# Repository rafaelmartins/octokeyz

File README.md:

# octokeyz

A USB macropad you program with Go.

For documentation please visit: https://octokeyz.rgm.io/

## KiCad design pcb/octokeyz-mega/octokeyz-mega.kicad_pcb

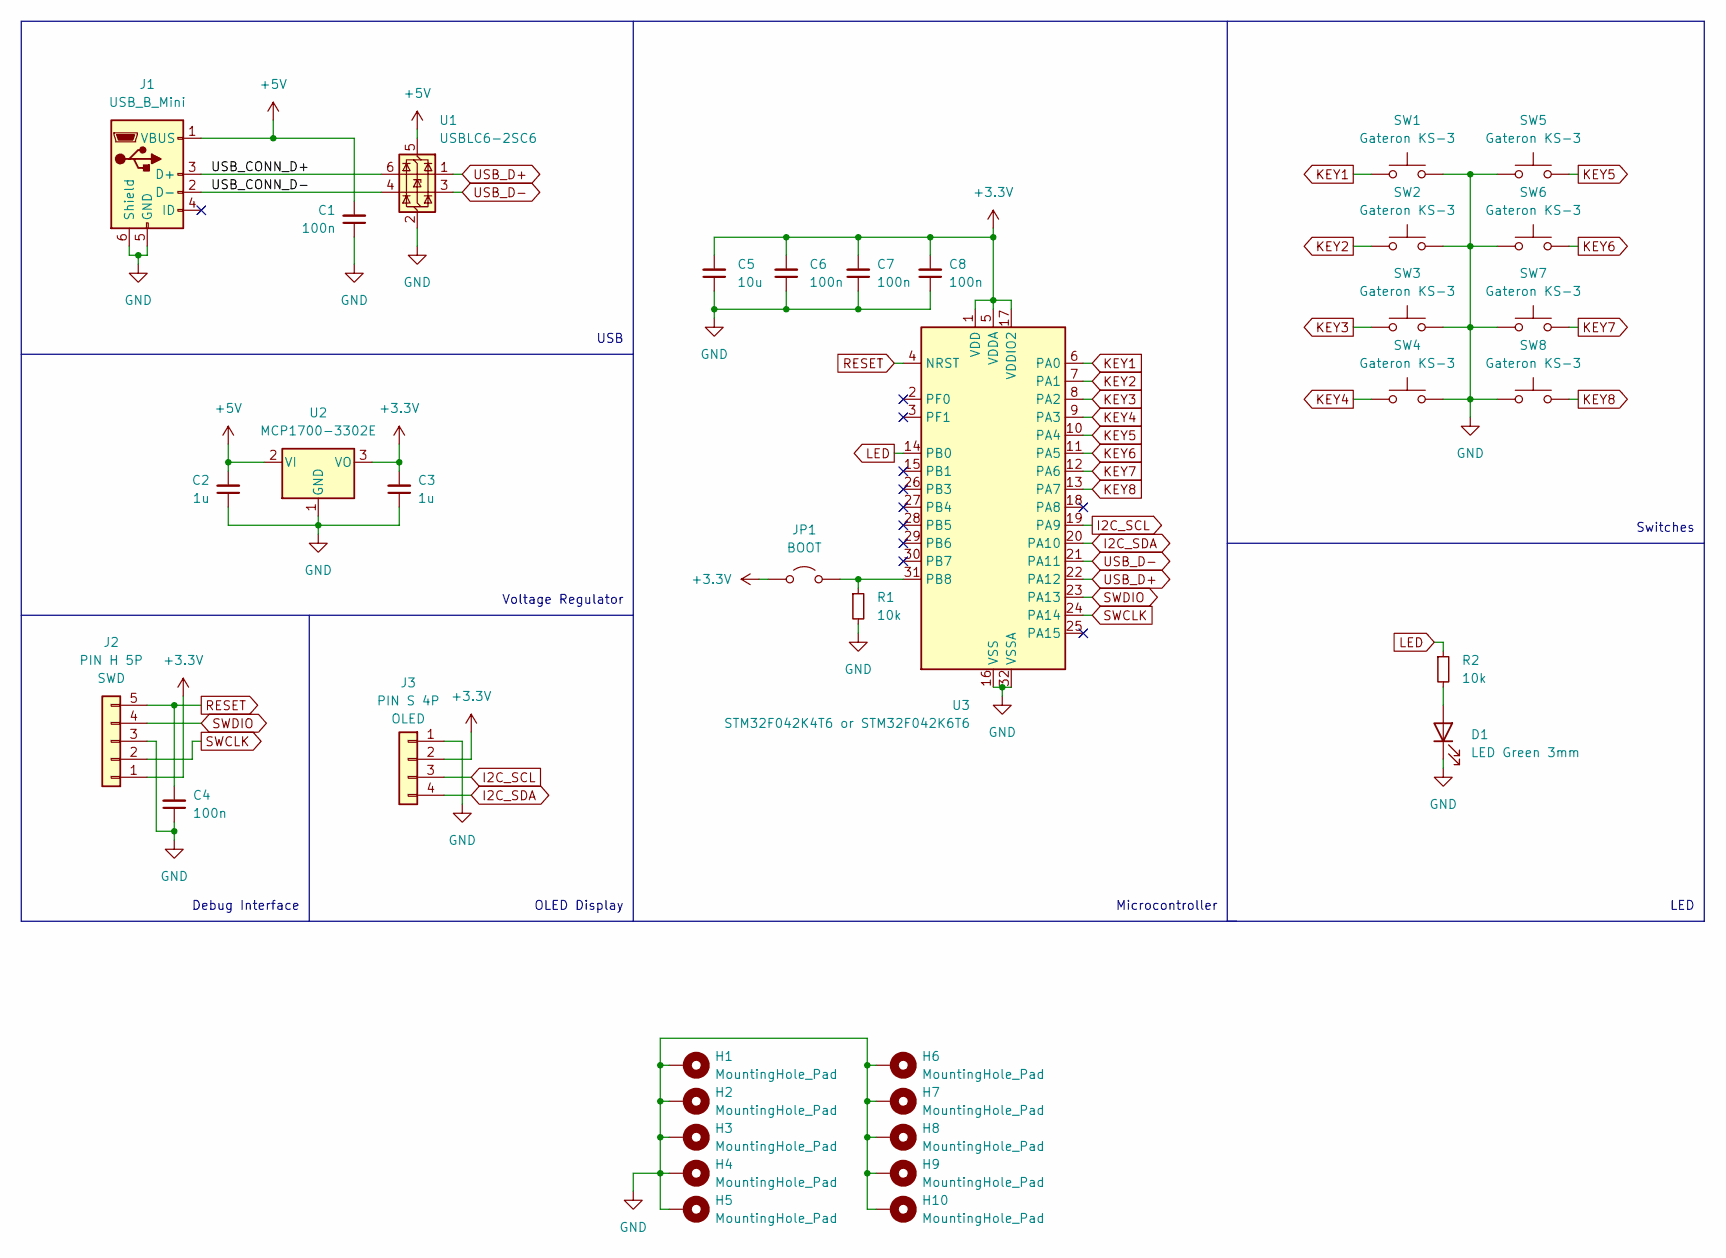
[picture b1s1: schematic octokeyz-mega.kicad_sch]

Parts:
C1, C4, C6, C7, C8: 100n; C_TDK_FA28; MPN FA28X7R1H104KNU06
C2, C3: 1u; C_TDK_FA28; MPN FA28X7R1E105KRU06
C5: 10u; C_TDK_FA26; MPN FA26X7R1E106KRU06
D1: LED Green 3mm; LED_D3.0mm; MPN OVLBG4C7
H1, H2, H3, H4, H5, H6, H7, H8, H9, H10: MountingHole_Pad; MountingHole_2.2mm_M2_Pad_Via
J1: USB_B_Mini; USB_Mini-B_PTH; MPN GMSB0522132EU
J2: PIN H 5P; PinHeader_1x05_P2.54mm_Horizontal
J3: PIN S 4P; PinSocket_1x04_P2.54mm_Vertical; MPN PPPC041LFBN-RC
JP1: BOOT; PinHeader_1x02_P2.54mm_Horizontal
R1, R2: 10k; R_YAGEO_MFR-25FTE52_Horizontal; MPN MFR-25FTE52-10K
SW1, SW2, SW3, SW4, SW5, SW6, SW7, SW8: Gateron KS-3; SW_Cherry_MX_1.00u_PCB; MPN Gateron KS-3
U1: USBLC6-2SC6; SOT-23-6; MPN USBLC6-2SC6
U2: MCP1700-3302E; TO-92_Inline_Wide; MPN MCP1700-3302E/TO
U3: STM32F042K4T6 or STM32F042K6T6; LQFP-32_7x7mm_P0.8mm; MPN STM32F042K6T6

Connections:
+3.3V: C3.2, C5.2, C6.2, C7.2, C8.2, J2.1, J3.2, JP1.2 (B), U2.3 (VO), U3.1 (VDD), U3.5 (VDDA), U3.17 (VDDIO2)
+5V: C1.2, C2.2, J1.1 (VBUS), U1.5 (VBUS), U2.2 (VI)
/USB_CONN_D+: J1.3 (D+), U1.6 (I/O1)
/USB_CONN_D-: J1.2 (D-), U1.4 (I/O2)
GND: C1.1, C2.1, C3.1, C4.1, C5.1, C6.1, C7.1, C8.1, D1.1 (K), H1.1, H2.1, H3.1, H4.1, H5.1, H6.1, H7.1, H8.1, H9.1, H10.1, J1.5 (GND), J1.6 (Shield), J2.3, J3.1, R1.2, SW1.2, SW2.2, SW3.2, SW4.2, SW5.2, SW6.2, SW7.2, SW8.2, U1.2 (GND), U2.1 (GND), U3.16 (VSS), U3.32 (VSSA)
I2C_SCL: J3.3, U3.19 (PA9)
I2C_SDA: J3.4, U3.20 (PA10)
KEY1: SW1.1, U3.6 (PA0)
KEY2: SW2.1, U3.7 (PA1)
KEY3: SW3.1, U3.8 (PA2)
KEY4: SW4.1, U3.9 (PA3)
KEY5: SW5.1, U3.10 (PA4)
KEY6: SW6.1, U3.11 (PA5)
KEY7: SW7.1, U3.12 (PA6)
KEY8: SW8.1, U3.13 (PA7)
LED: R2.1, U3.14 (PB0)
unnamed: D1.2 (A), R2.2
unnamed: JP1.1 (A), R1.1, U3.31 (PB8)
RESET: C4.2, J2.5, U3.4 (NRST)
SWCLK: J2.2, U3.24 (PA14)
SWDIO: J2.4, U3.23 (PA13)
USB_D+: U1.1 (I/O1), U3.22 (PA12)
USB_D-: U1.3 (I/O2), U3.21 (PA11)

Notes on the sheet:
Switches
OLED Display
Microcontroller
LED
Debug Interface
USB
Voltage Regulator

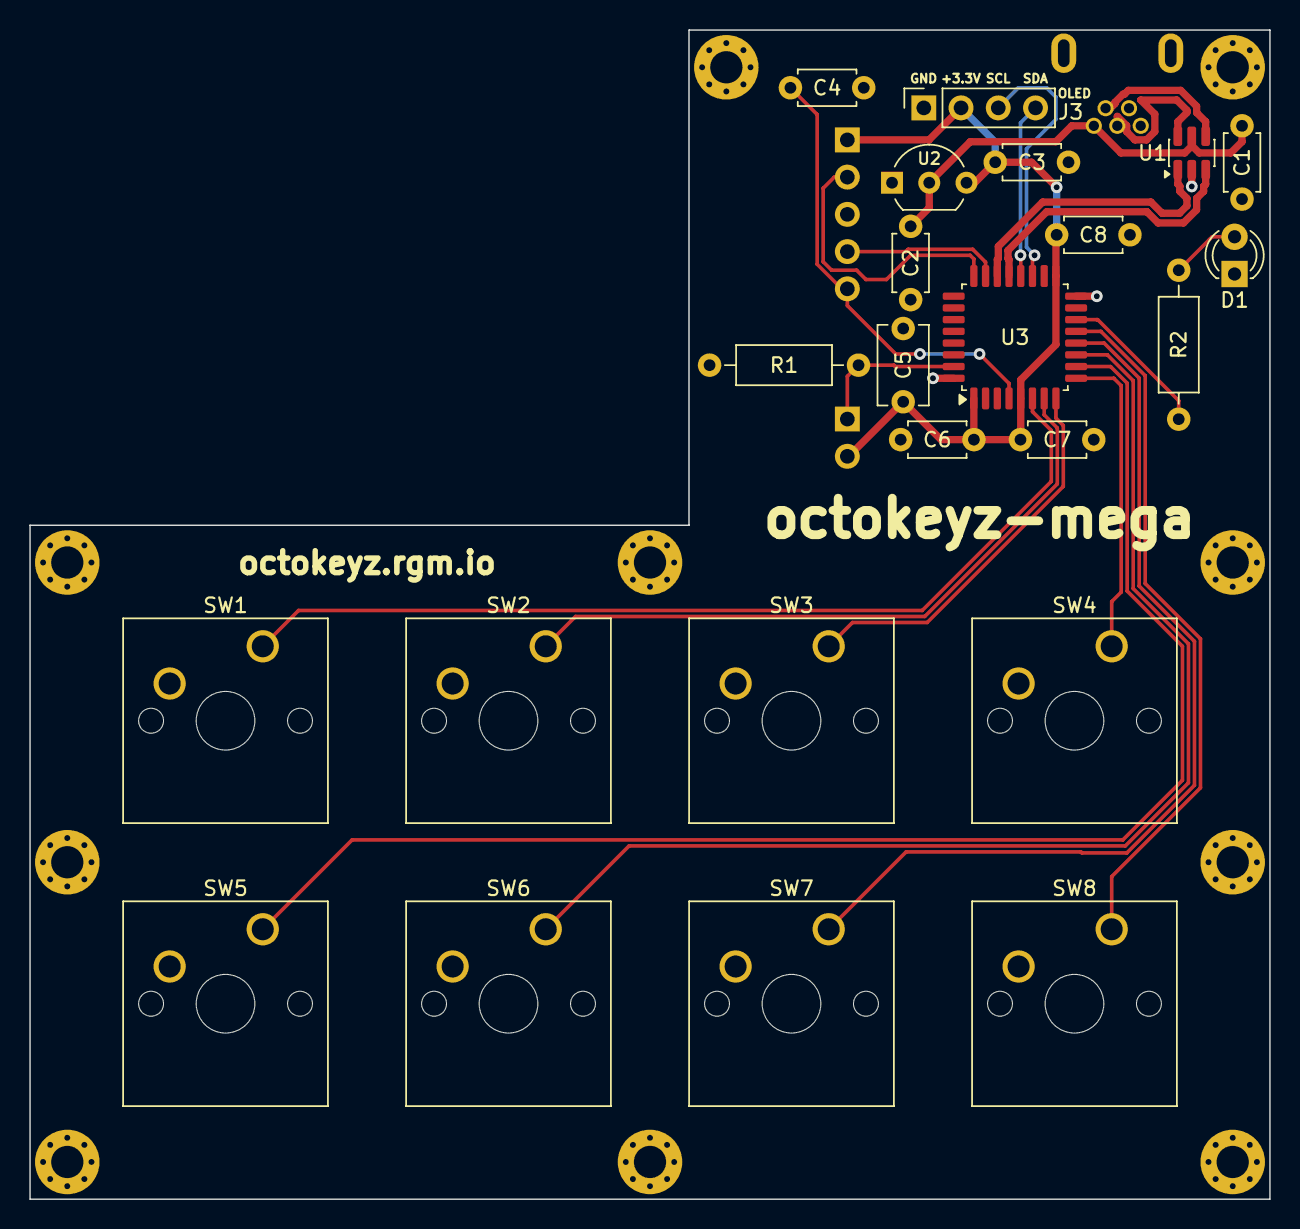
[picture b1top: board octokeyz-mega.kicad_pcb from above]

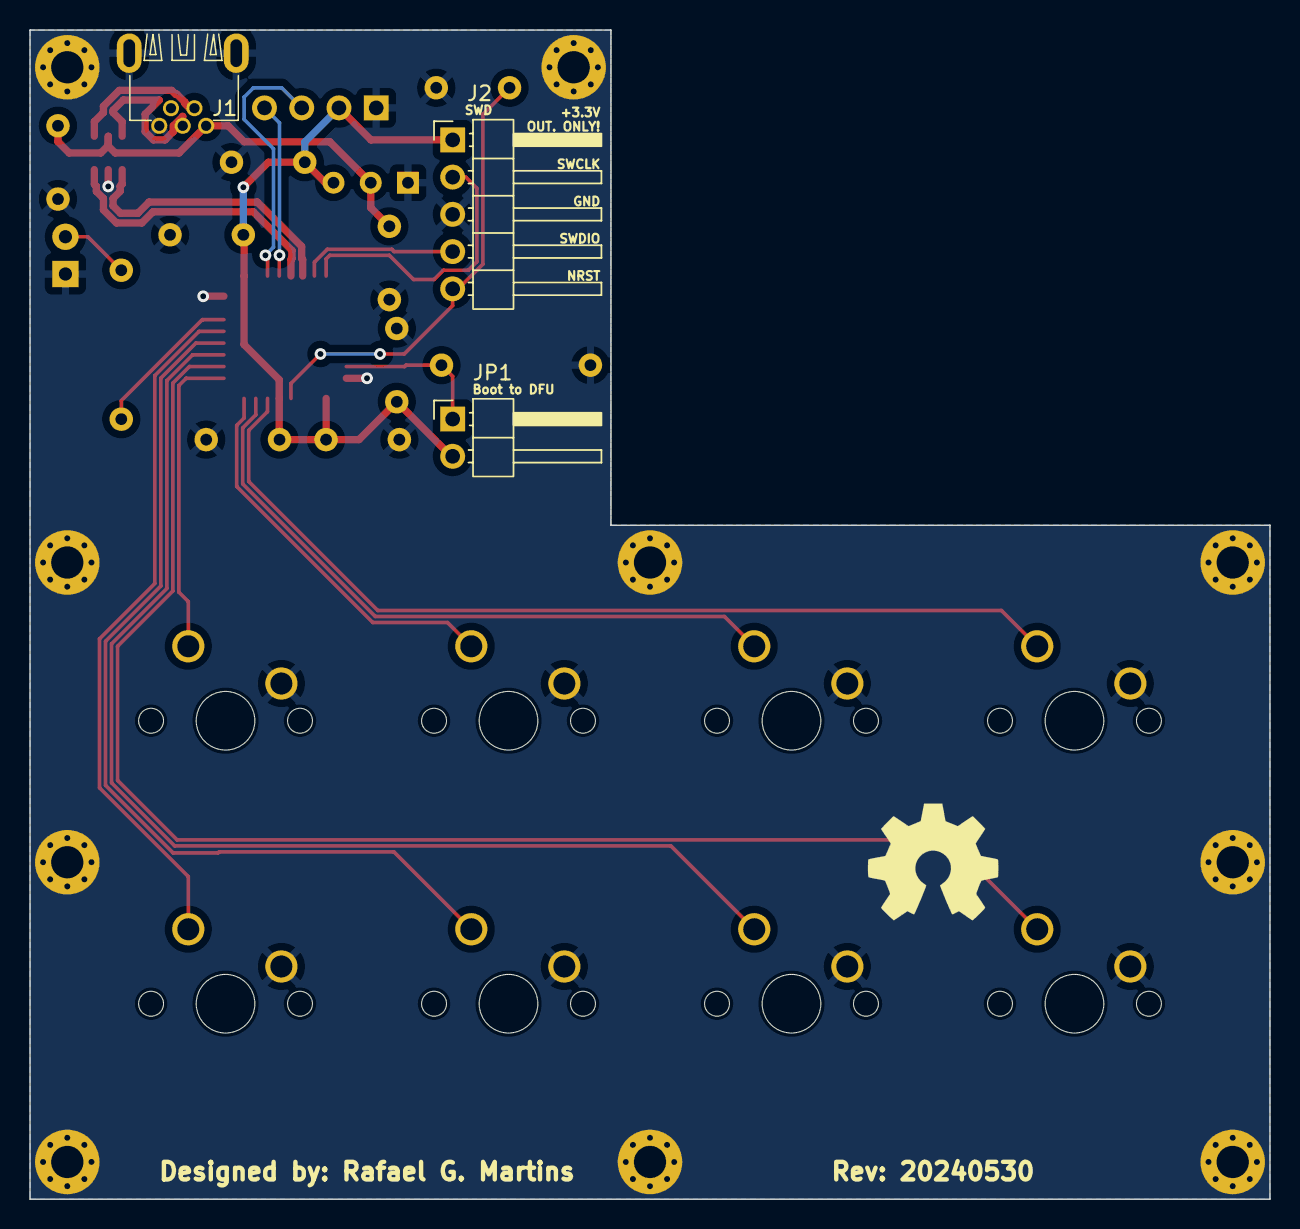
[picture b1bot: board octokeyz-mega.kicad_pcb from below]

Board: 2 copper layers, 84.6 x 79.8 mm, 36 parts (3 on the bottom side), 23 nets.

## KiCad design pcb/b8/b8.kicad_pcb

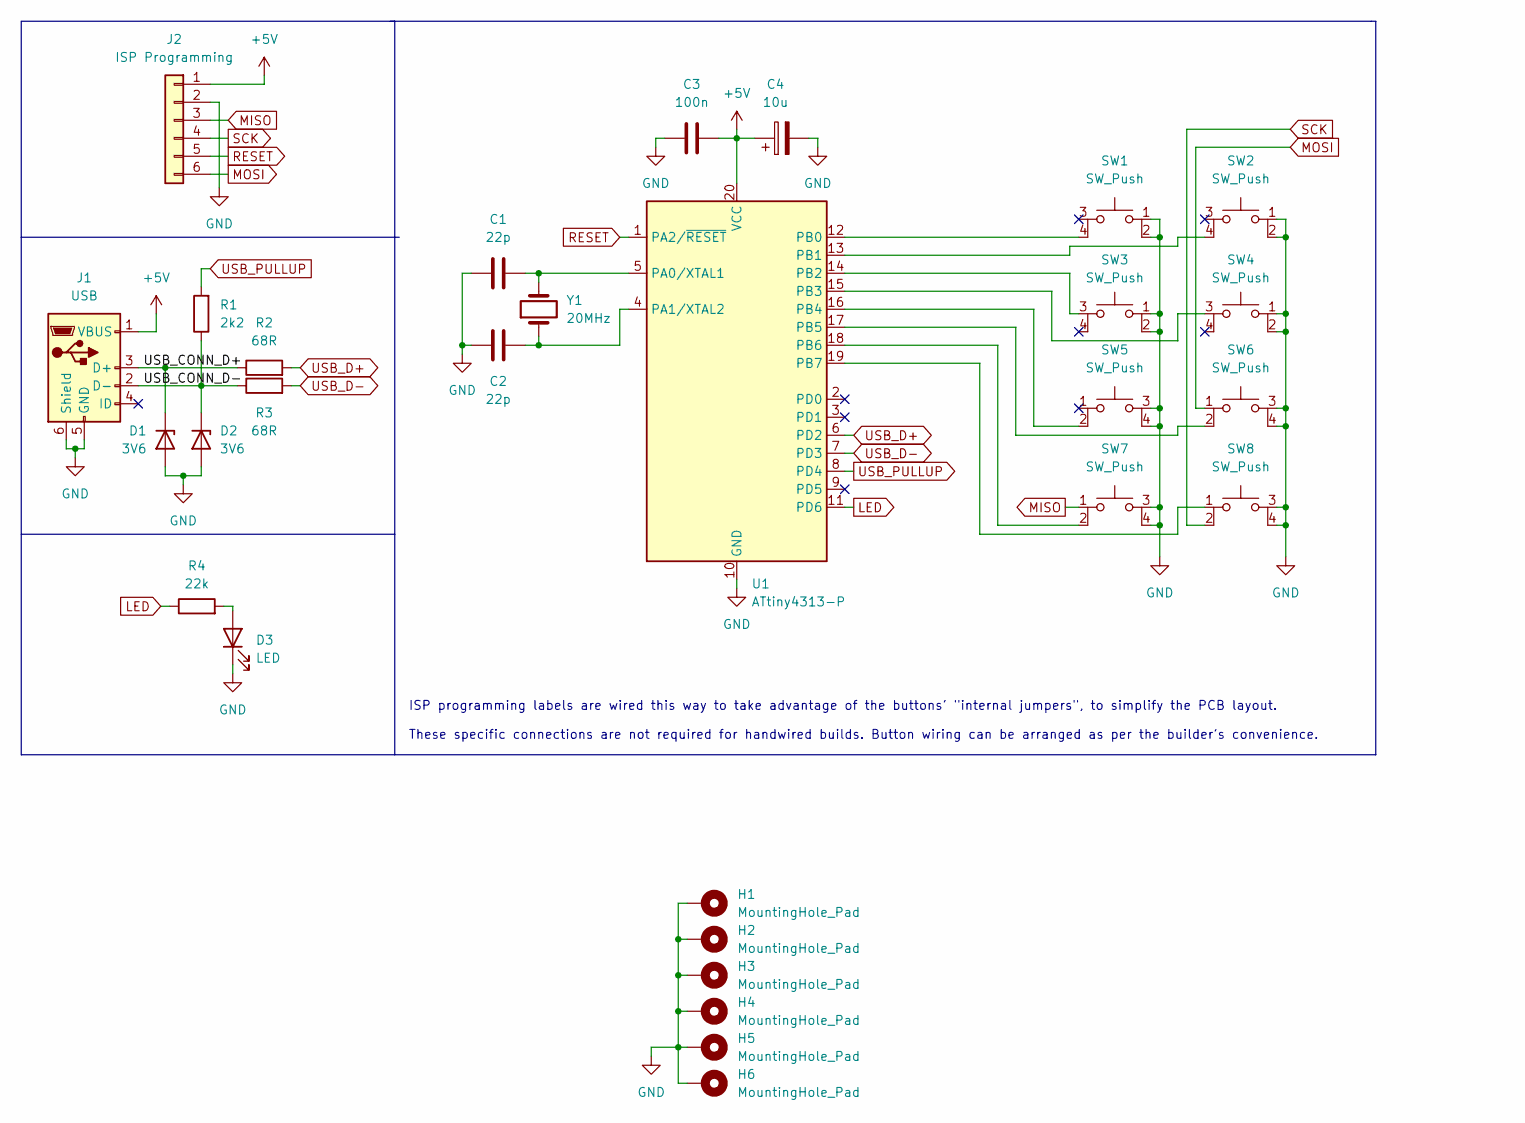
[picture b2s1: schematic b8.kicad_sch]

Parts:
C1, C2: 22p; C_Disc_D3.0mm_W1.6mm_P2.50mm
C3: 100n; C_TDK_FA28
C4: 10u; CP_Radial_D5.0mm_P2.50mm_Horizontal
D1, D2: 3V6; D_DO-35_SOD27_P7.62mm_Horizontal
D3: LED; LED_D3.0mm
H1, H2, H3, H4, H5, H6: MountingHole_Pad; MountingHole_2.2mm_M2_Pad_Via
J1: USB; USB_Mini-B_PTH
J2: ISP Programming; PinHeader_1x06_P2.54mm_Horizontal
R1: 2k2; R_YAGEO_MFR-25FTE52_Horizontal
R2, R3: 68R; R_YAGEO_MFR-25FTE52_Horizontal
R4: 22k; R_YAGEO_MFR-25FTE52_Horizontal
SW1, SW2, SW3, SW4, SW5, SW6, SW7, SW8: SW_Push; SW_PUSH-12mm
U1: ATtiny4313-P; DIP-20_W7.62mm
Y1: 20MHz; Crystal_HC49-4H_Vertical

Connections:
+5V: C3.2, C4.1, J1.1 (VBUS), J2.1, U1.20 (VCC)
/USB_CONN_D+: D1.1 (K), J1.3 (D+), R2.1
/USB_CONN_D-: D2.1 (K), J1.2 (D-), R1.1, R3.1
GND: C1.1, C2.1, C3.1, C4.2, D1.2 (A), D2.2 (A), D3.1 (K), H1.1, H2.1, H3.1, H4.1, H5.1, H6.1, J1.5 (GND), J1.6 (Shield), J2.2, SW1.1, SW1.2, SW2.1, SW2.2, SW3.1, SW3.2, SW4.1, SW4.2, SW5.3, SW5.4, SW6.3, SW6.4, SW7.3, SW7.4, SW8.3, SW8.4, U1.10 (GND)
LED: R4.1, U1.11 (PD6)
MISO: J2.3, SW7.1
MOSI: J2.6, SW6.1
unnamed: D3.2 (A), R4.2
unnamed: C1.2, U1.5 (PA0/XTAL1), Y1.2
unnamed: C2.2, U1.4 (PA1/XTAL2), Y1.1
unnamed: SW1.4, U1.12 (PB0)
unnamed: SW2.4, U1.13 (PB1)
unnamed: SW3.3, U1.14 (PB2)
unnamed: SW4.3, U1.15 (PB3)
unnamed: SW5.2, U1.16 (PB4)
unnamed: SW6.2, U1.17 (PB5)
unnamed: SW7.2, U1.18 (PB6)
unnamed: SW8.1, U1.19 (PB7)
RESET: J2.5, U1.1 (PA2/~RESET)
SCK: J2.4, SW8.2
USB_D+: R2.2, U1.6 (PD2)
USB_D-: R3.2, U1.7 (PD3)
USB_PULLUP: R1.2, U1.8 (PD4)

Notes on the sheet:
ISP programming labels are wired this way to take advantage of the buttons' "internal jumpers", to simplify the PCB layout. These specific connections are not required for handwired builds. Button wiring can be arranged as per the builder's convenience.

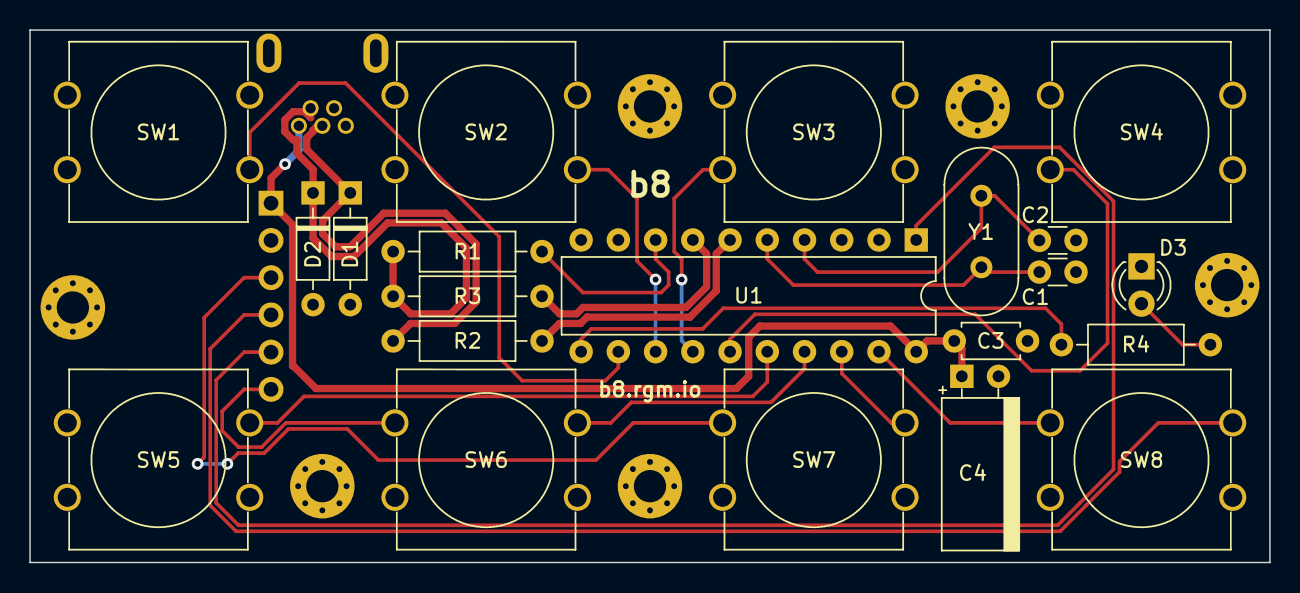
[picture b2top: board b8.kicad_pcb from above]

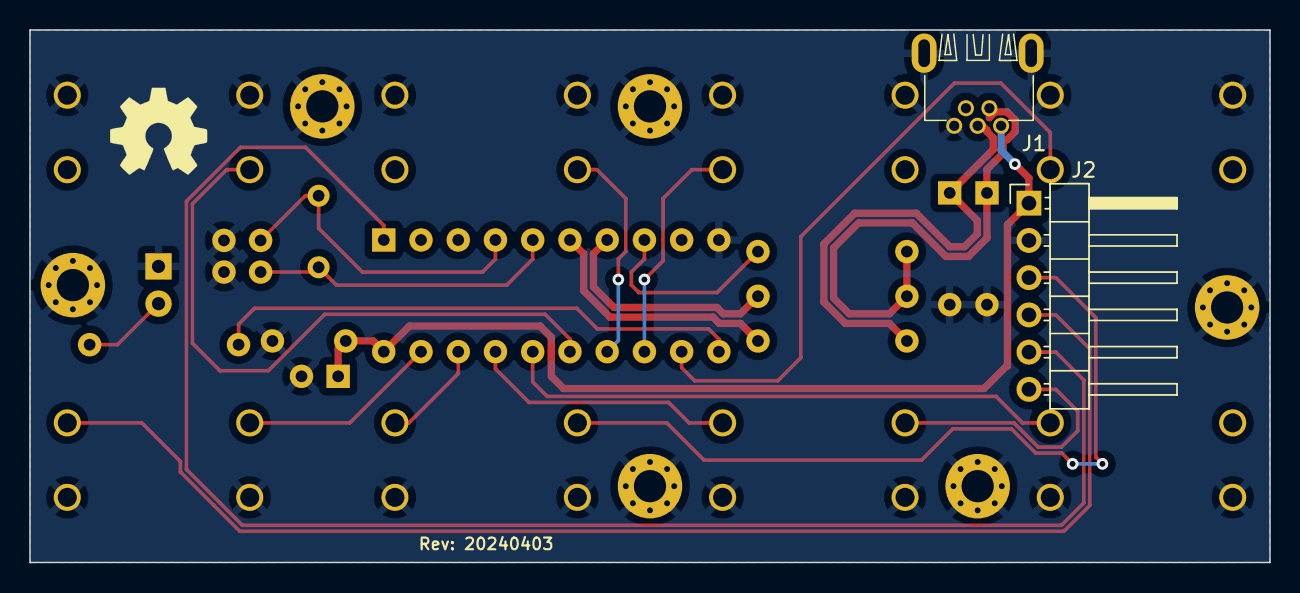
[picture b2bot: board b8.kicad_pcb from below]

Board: 2 copper layers, 84.6 x 36.3 mm, 29 parts (2 on the bottom side), 23 nets.

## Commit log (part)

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2022-10-18 readme: added prototype picture
2022-10-21 pcb: revision 1.0
2022-10-21 3d-models: current models are for my handmade prototype
2022-10-21 firmware: build firmware for attiny2313a
    firmware built for attiny2313 works fine, because we are not using any
    of the new registers, but the generated code is slightly different.
2022-10-21 go: improve button handlers
    this is not 100% safe yet. Event.WaitForRelease may block in a weird
    state if the "button up" event is missed.
2022-10-21 go: ignore "button down" event if some "button up" is queued
    this way it is possible to get out of a Event.WaitForRelease deadlock by
    pressing the button again.
2022-10-22 go: rewrote event handling
2022-10-24 go: split linux/evdev code into internal package
2022-10-24 go: added windows support
2022-10-24 go: improve event handling to avoid panic
2022-10-24 fixed license. only firmware is GPL
2022-10-26 go: initialize buttons lazily
2022-10-29 go: internal: usb: improve event interface
2022-10-29 go: support writing to led
2022-10-31 3d-models: add 3d-printable models designed for pcb rev 1.0
2022-10-31 go: added helper handler to use a button as modifier
2022-11-03 firmware: use "Usage Multi Mode Indicator" selector for led
    this allows the client to request the led to blink or flash without
    having to control that manually.
    golang library not supporting this yet.
    this also improves the led handling and the firmware code in general.
    when turning on the device, the led will stay on until the host sets its
    address.
2022-11-03 go: support led handling features from newer firmware
    this also rewrites the internal usb library to use hidraw instead of
    evdev on linux, and also reduces the report descriptor parsing, to make
    things simpler. we don't need to be generic, as we only support our own
    device.
2022-11-15 go: internal: usbhid: fix some error messages
2022-11-15 go: internal: usbhid: linux: implement exclusive lock
2022-11-23 go: internal: usbhid: windows: implement exclusive lock
2022-12-03 go: reimplement modifier
2022-12-06 firmware: unbundle avr-cmake and v-usb
2022-12-27 firmware: add automatically generated serial number
    the serial number is generated from non-initialized flash memory, which
    is not very reliable, and stored in eeprom. we may change this algorithm
    at some point.
    also, the code that implements this won't fit the attiny2313. devices
    using it won't have serial numbers, and are limited to one unit
    connected per computer.
2022-12-27 go: use serial number
2022-12-27 README: improvements
2022-12-27 README: more improvements
2022-12-30 pcb: revision 1.1
    this revision adds a 6th pin to ISP programming header, to allow usage
    of official Microchip probes, like PICKit 4. It also fixes alignment and
    dimensions of the buttons.
2023-01-06 3d-models: adapt 3d models to pcb rev 1.1
2023-01-06 firmware: add fuses and lockbits to elf
2023-01-06 go: unbundle usbhid library
2023-01-22 go: added documentation, some interface changes
    renamed ListDevices to Enumerate. changed version number handling.
2023-01-24 firmware: initialize serial number if value is 0
2023-01-24 go: fix typos
2023-01-24 go: upgrade usbhid
2023-03-22 go: improve button channel handling
2023-03-22 firmware: improve serial number generation
2023-08-16 go: improve error reporting when adding handler
2023-08-17 firmware: go: use usb pid from openmoko
    We still keep some compatibility with the old VID/PID pair. For our
    dedicated pair we won't check manufacturer and product anymore.
    PR: https://github.com/openmoko/openmoko-usb-oui/pull/53
2024-02-24 go: allow custom error handling for button handlers
2024-02-24 fix readme example
2024-04-03 pcb: port to kicad 7
2024-04-04 pcb: b8-mega: revision 20240403
    this is a new pcb variant, that uses mechanical keyboard switches and
    introduces a monochrome oled display. as it uses an STM32 instead of the
    AVR from original b8 pcb, there's no public firmware for it yet.
2024-04-04 3d-models: move original b8 enclosure to b8 folder, remove prototype
2024-04-04 pcb: b8: revision 20240403
    some minor pcb fixes. this also moves the pcb files to pcb/b8, preparing
    to introduce other pcb variants. this also moves the kicad library to
    pcb/lib and adds the missing LICENSE file.
2024-04-14 3d-models: b8-mega: new enclosure for the b8-mega variant
2024-04-14 firmware: move to firmware/b8
    preparing to add firmware for a new model
2024-04-14 firmware: b8-mega: initial implementation
    this is a firmware for STM32F042, that works very similar to the
    original b8 firmware, but also includes a display. it does not works
    properly with the current go library, because I discovered a descriptor
    error in the original b8 firmware, that was not yet fixed there.
2024-04-15 firmware: pcb fix usb descriptor mistake.
    this also bumps the device number to 01.01, matching b8-mega
2024-04-15 go: support b8-mega
2024-04-15 firmware: b8-mega: fix usb watchdog reset
2024-04-15 upgrade usbhid library
2024-05-11 3d-models: b8-mega: remove unused include
2024-05-11 3d-models: lib: ssd1306: fix screen position
2024-05-11 3d-models: b8-mega: added base model
2024-05-28 firmware: b8-mega: small display improvements
2024-05-28 go: added method to return number of characters per line
2024-05-28 3d-models: fix copyright
2024-05-29 build: generate ibom and upload to github pages
2024-05-29 build: fix pages yaml
2024-05-29 go: added missing LedState type declaration
2024-05-31 go: stop supporting old shared usb vid/pid
2024-06-01 pcb: octokeyz: revision 20240601
    minor changes.
2024-06-01 pcb: octokeyz-mega: revision 20240601
    minor changes.
2024-06-06 firmware: octokeyz-mega: upgrade usbd-fs-stm32
2024-06-09 firmware: octokeyz-mega: reset to bootloader using a key sequence
2024-06-09 firmware: octokeyz-mega: use vendor usage pages
2024-06-09 firmware: octokeyz-mega: minor fix
2024-06-09 go: clear display and turn led off on close
2024-06-09 firmware: octokeyz-mega: remove usb watchdog
    it used to work as expected only in some old linux kernel versions, now
    not even there.
2024-06-09 firmware: octokeyz-mega: avoid external sw reset to load bootloader
2024-06-15 firmware: octokeyz-mega: support boards without a display
2024-06-15 firmware: octokeyz-mega: simplify bootloader combo
2024-06-15 3d-models: octokeyz-mega: minor fixes
2024-06-15 3d-models: octokeyz-mega: add test script
2024-06-16 Revert "3d-models: octokeyz: support square keycaps"
    This reverts commit 6c08e28fb599013f4a4b72e768e422f4d81155a3.
2024-06-16 pcb: octokeyz: revision 20240616
    use stm32 instead of avr microcontroller. the prices are similar
    nowadays, and it will allow us to have a single DFU-capable and
    BSD-licensed firmware usable by all boards.
    the board outline and the position of buttons and connectors is the
    same, any existing cases should still fit correctly.
2024-06-16 README: remove references to old firmware
2024-06-16 firmware: remove old attiny firmware
2024-06-16 firmware: rename waratah config file
2024-06-21 readme fixes
2024-06-22 firmware: rename from "octokeys-mega" to "octokeyz"
2024-06-23 firmware: fix bootloader issues when building with -O3
2024-06-23 pcb: added STM32F042K4T6 as microcontroller alternative
    as this is a purely cosmetic change that doesn't affects the produced
    boards I do not bumped revision number neither re-generated gerber
    files.
2024-06-25 firmware: fix splash screen, limit linker script to 16k flash
2024-06-25 firmware: added version to splash screen
2024-06-26 pcb: generate ibom with cmake
2024-06-26 build: fetch whole repository history
2024-06-26 upgrade cmsis
2024-07-11 reorganize licenses
2024-07-12 firmware: use cmake_cmsis_stm32
2024-07-12 cmake: split version generation into a separated script
2024-07-12 cmake: improve dist generation
2024-07-12 build: initial main workflow
2024-07-12 build: typo
2024-07-12 build: fix sha256sum check
2024-07-12 build: added missing dependency
2024-07-12 build: move source checkout to a subdir, upgrade cmake-cmsis-stm32
2024-07-12 build: fix ibom generation without a display
2024-07-12 build: force ubuntu-24.04
2024-07-12 build: run dfuse-pack from git
2024-07-12 build: fix release type
2024-07-13 cmake: improve git-version-gen.cmake
2024-07-25 cmake: upgrade cmake-cmsis-stm32
2024-07-25 go: upgrade usbhid library
    now it supports darwin/macos \o/
2024-07-29 go: stop listening to hid input events when device is closed
2024-07-29 firmware: upgrade cmake-cmsis-stm32
2024-08-10 firmware: reimplement display driver
    this replaces the backlog implementation with a double buffer implementation,
    and improves the data handling while data is already being sent, avoiding
    dangling content in the screen.
2024-08-18 firmware: display: add a usb out report to clear display with delay.
    the delay is set in milliseconds, limited to 65535ms. this is the maximum
    delay applied when clearing the display: if any write operation happens while
    the delay is ongoing, the display is erased immediately before writing the
    new data. no new data is delayed or lost, making this feature very suitable for
    notifications.
2024-08-18 build: let cmake-cmsis-stm32 pick its own dfuse-pack script
2024-08-24 go: improve error handling. upgrade usbhid dependency
2024-08-24 go: support "display clear with delay" feature.
2024-11-03 cmake: fix readme typos
2024-11-03 share: udev: assign hidraw devices to plugdev group
    TAG+="uaccess" is not enough because systems without a display manager/tty
    won't assign seats to login sessions.
2024-11-11 firmware: upgrade usbd-fs-stm32
2024-11-14 go: upgrade dependencies
2024-11-15 firmware: implement hid idle support
2025-03-02 readme: fix spelling/grammar
2025-03-02 rename go client library to rafaelmartins.com/p/octokeyz/go/octokeyz
2025-03-02 moved go client to its own repository
2025-03-02 fix go client links
2025-03-02 upgrade usbd-fs-stm32 and cmake-cmsis-stm32
2025-06-02 firmware: fix clock for i2c peripheral
2025-06-14 firmware: display: wait for display to become available
    SSD1306 displays from some batches will take some time to get ready to accept
    I2C communication, apply some (limited) delay when receiving NACKs for address
    transmissions.
    this also reimplements the automatic detection of display connected to the I2C
    bus.
2025-06-14 firmware: display: restart i2c peripheral on detection timeout
2025-06-14 firmware: display: remove unnecessary volatile declaration
    let the compiler do its job here.
2026-01-21 pcb: octokeyz-mega: fix revision 20240601 -> 20240530
    after almost two years, I was going to assemble a new unit for myself when I realized that
    the revision printed to the board was different from the schematics. since the boards are
    manufactured for very long, its source file contains the same revision and this revision was
    never released before, the easiest fix is to edit the schematics and rename the gerber zip
    file without changing anything on the boards.
    the revision 20240601 never existed :-)
2026-01-29 pcb: fix some libraries for kicad 9.0.7
    this makes no significant changes to physical layers, no revision changes.
2026-02-04 pcb: change soldermask color to blue in physical stackup
2026-02-04 build: generate assets and publish to github pages
    must rework the cmake generated tarballs
2026-02-08 docs: revamp project documentation. this is now hosted at rafaelmartins.com
2026-02-08 docs: minor fix
2026-02-10 doc: fixes
2026-02-21 build: rename actionrafaelmartins/website/{kicad,hardware}
2026-02-22 Revert "build: rename actionrafaelmartins/website/{kicad,hardware}"
    This reverts commit 4f2cdf5d6cc2d84ccabd70681ddec2acb4c06ab4.
2026-02-22 pcb: update asset gen config files
2026-02-24 cmake: typo
2026-02-24 build: rework whole build system
2026-02-27 build: trying to implement rolling releases
2026-02-27 build: fix minimal cmake version
2026-02-27 docs: update
2026-03-16 firmware: fix version on splash screen
2026-04-09 update cmake stuff

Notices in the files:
pcb/b8.kicad_sch:
Released under CERN Open Hardware Licence Version 2 - Strongly Reciprocal
